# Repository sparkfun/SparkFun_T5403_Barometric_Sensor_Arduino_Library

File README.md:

Sparkfun T5403 Barometric Sensor Breakout Arduino Library
=======================================================

[*SEN-12039*](https://www.sparkfun.com/products/12039)

Library and example code for the Epcos T5403 barometric pressure sensor.

Repository Contents
-------------------

* **/examples** - Example sketches for the library (.ino). Run these from the Arduino IDE. 
* **/src** - Source files for the library (.cpp, .h).
* **keywords.txt** - Keywords from this library that will be highlighted in the Arduino IDE. 
* **library.properties** - General library properties for the Arduino package manager. 

Documentation
--------------
* **[Installing an Arduino Library Guide](https://learn.sparkfun.com/tutorials/installing-an-arduino-library)** - Basic information on how to install an Arduino library.
* **[Product Repository](https://github.com/sparkfun/SparkFun_T5403_Barometric_Breakout)** - Main repository (including hardware files) for the SparkFun T5403 Barometric Sensor Breakout.
* **[Hookup Guide](https://learn.sparkfun.com/tutorials/t5403-barometric-pressure-sensor-hookup)** - Basic hookup guide for the T5403 Barometric Pressure Sensor.

Products that use this Library 
---------------------------------
* [SEN-12039](https://www.sparkfun.com/products/12039) - T5403 Barometric Sensor Breakout

Version History
----------------
* [1.0.1](https://github.com/sparkfun/SparkFun_T5403_Barometric_Sensor_Arduino_Library/tree/V_1.0.1) - Small clean-up, edits.
* [1.0](https://github.com/sparkfun/SparkFun_T5403_Barometric_Sensor_Arduino_Library/tree/V_1.0) - Initial Release

License Information
-------------------

This product is _**open source**_! 

The **code** is beerware; if you see me (or any other SparkFun employee) at the local, and you've found our code helpful, please buy us a round!

Please use, reuse, and modify these files as you see fit. Please maintain attribution to SparkFun Electronics and release anything derivative under the same license.

Distributed as-is; no warranty is given.

- Your friends at SparkFun.

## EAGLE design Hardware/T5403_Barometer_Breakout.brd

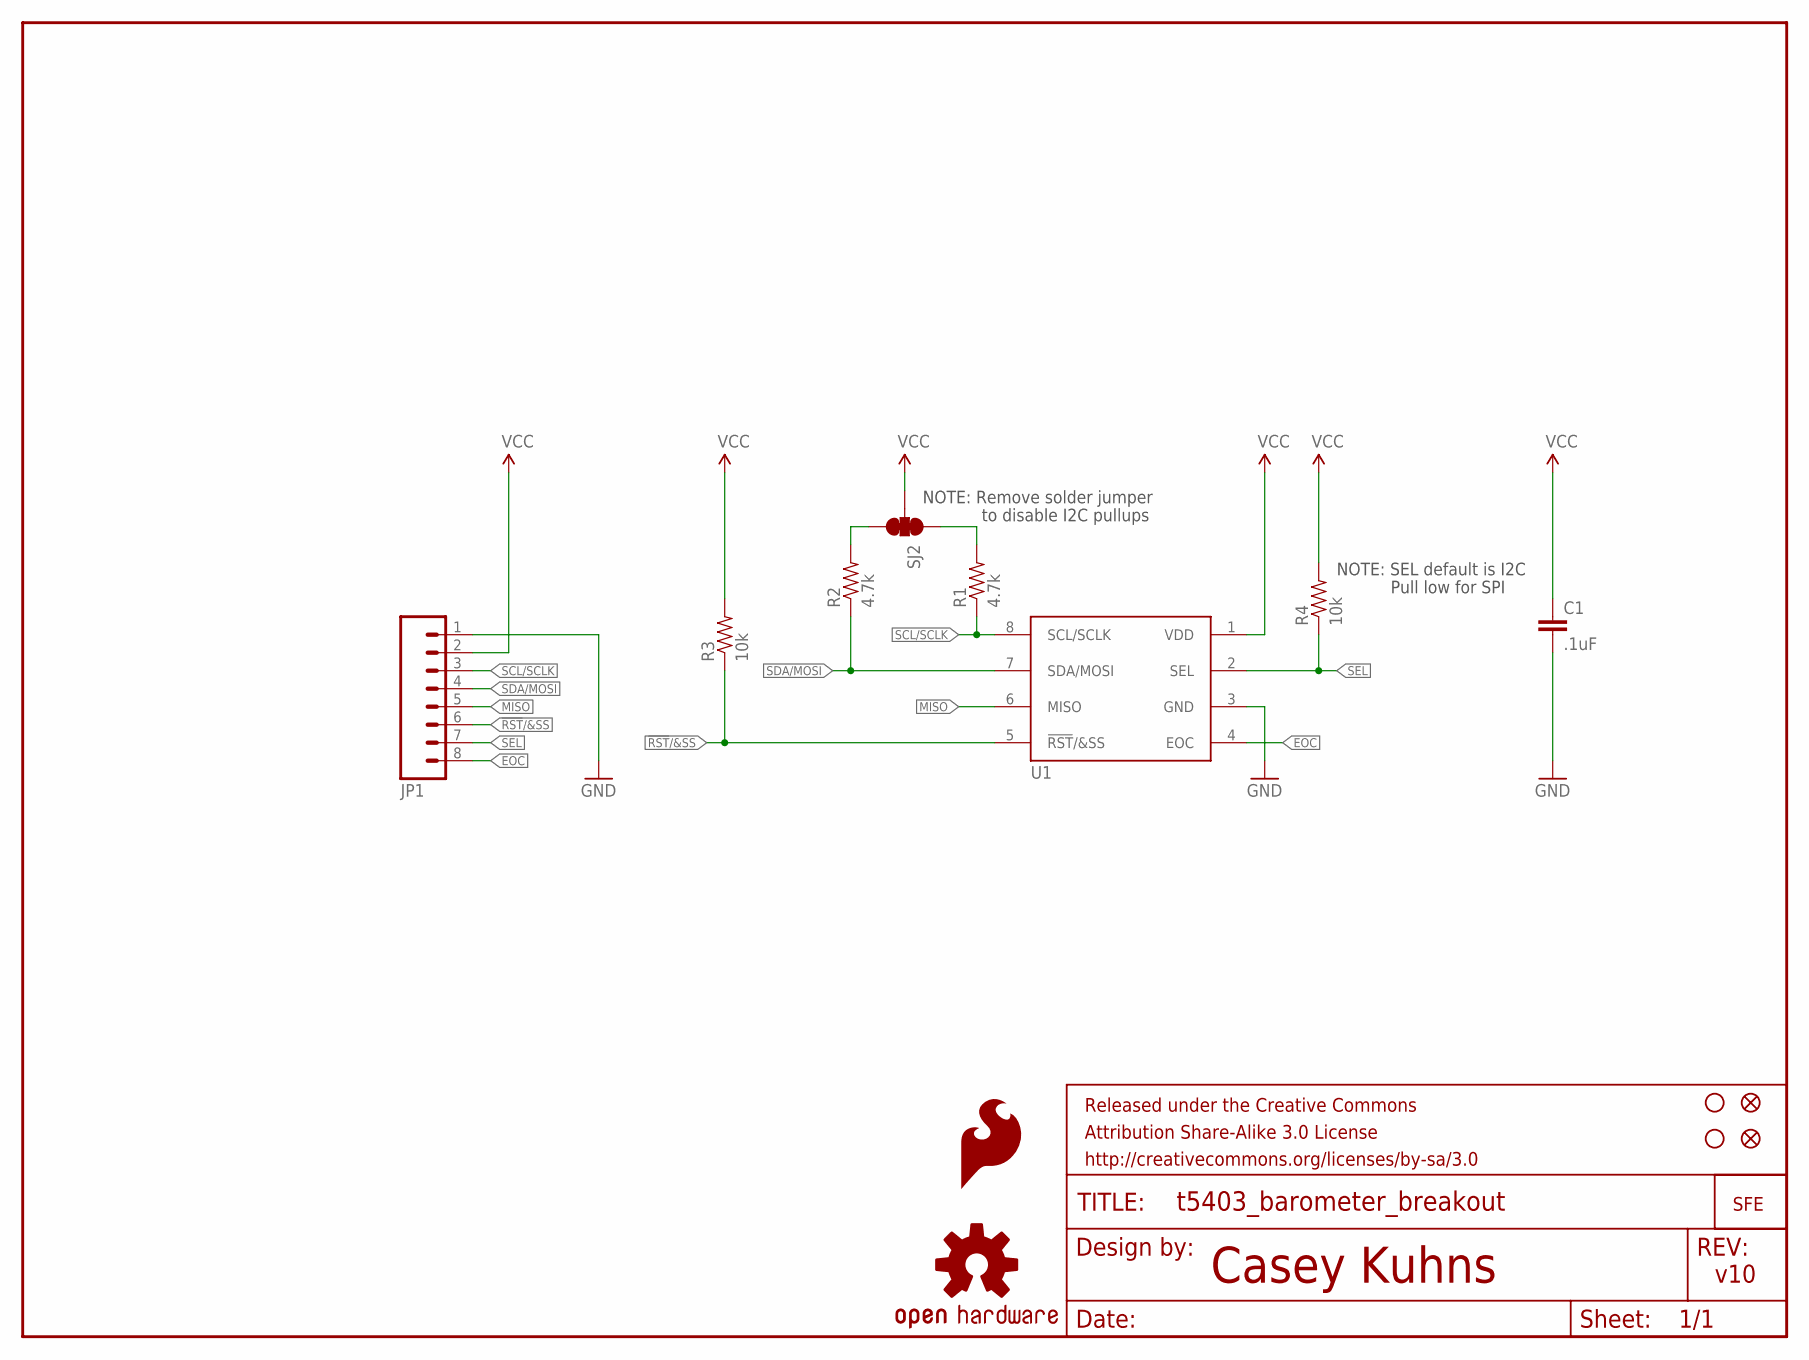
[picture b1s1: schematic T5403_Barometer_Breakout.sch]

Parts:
C1: .1uF; 0603-CAP
FID1, FID2: FIDUCIAL1X2; FIDUCIAL-1X2
FRAME1: FRAME-LETTER; CREATIVE_COMMONS
JP1: M081X08; 1X08
LOGO1: LOGO-SFENEW; SFE-NEW-WEBLOGO
LOGO2: OSHW-LOGOS; OSHW-LOGO-S
LOGO3: SFE_LOGO_FLAME.1_INCH; SFE_LOGO_FLAME_.1
R1, R2: 4.7k; 0603
R3, R4: 10k; 0603-RES
SJ2: SOLDERJUMPER_2WAYPASTE1&2&3; SJ_3_PASTE1&2&3
STANDOFF1, STANDOFF2: STAND-OFF
U1: T5400

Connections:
!RST!/&SS: JP1.6, R3.1, U1.5 (!RST!/&SS)
EOC: JP1.8, U1.4 (EOC)
GND: C1.2, JP1.1, U1.3 (GND)
MISO: JP1.5, U1.6 (MISO)
unnamed: R2.2, SJ2.3
unnamed: R1.2, SJ2.1
SCL/SCLK: JP1.3, R1.1, U1.8 (SCL/SCLK)
SDA/MOSI: JP1.4, R2.1, U1.7 (SDA/MOSI)
SEL: JP1.7, R4.1, U1.2 (SEL)
VCC: C1.1, JP1.2, R3.2, R4.2, SJ2.2, U1.1 (VDD)

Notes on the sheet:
Casey Kuhns
v10
NOTE: Remove solder jumper
to disable I2C pullups
NOTE: SEL default is I2C
Pull low for SPI

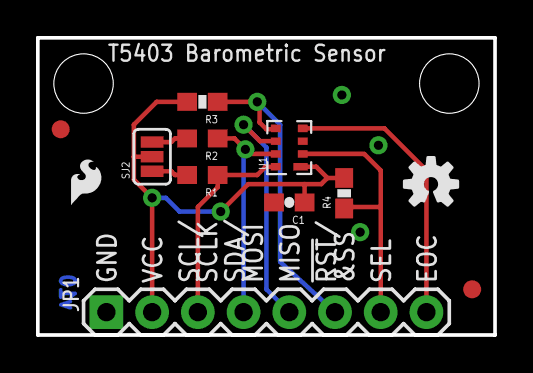
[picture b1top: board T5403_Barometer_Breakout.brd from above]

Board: 2 copper layers, 25.4 x 16.5 mm, 16 parts (1 on the bottom side), 10 nets.

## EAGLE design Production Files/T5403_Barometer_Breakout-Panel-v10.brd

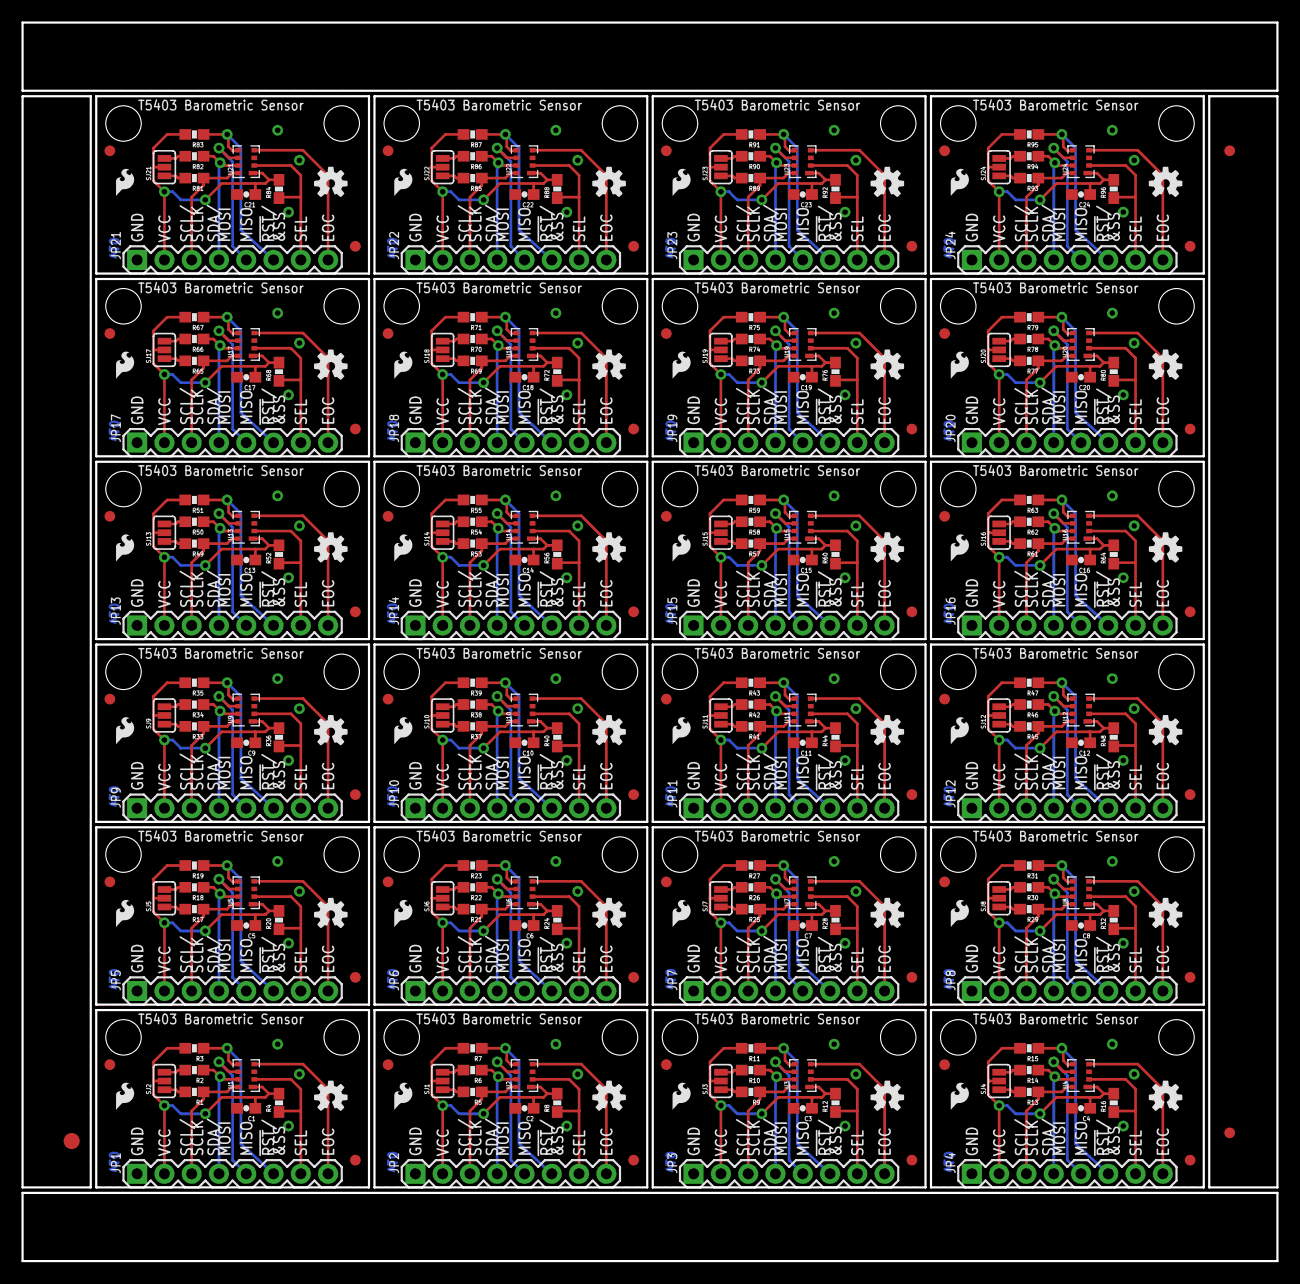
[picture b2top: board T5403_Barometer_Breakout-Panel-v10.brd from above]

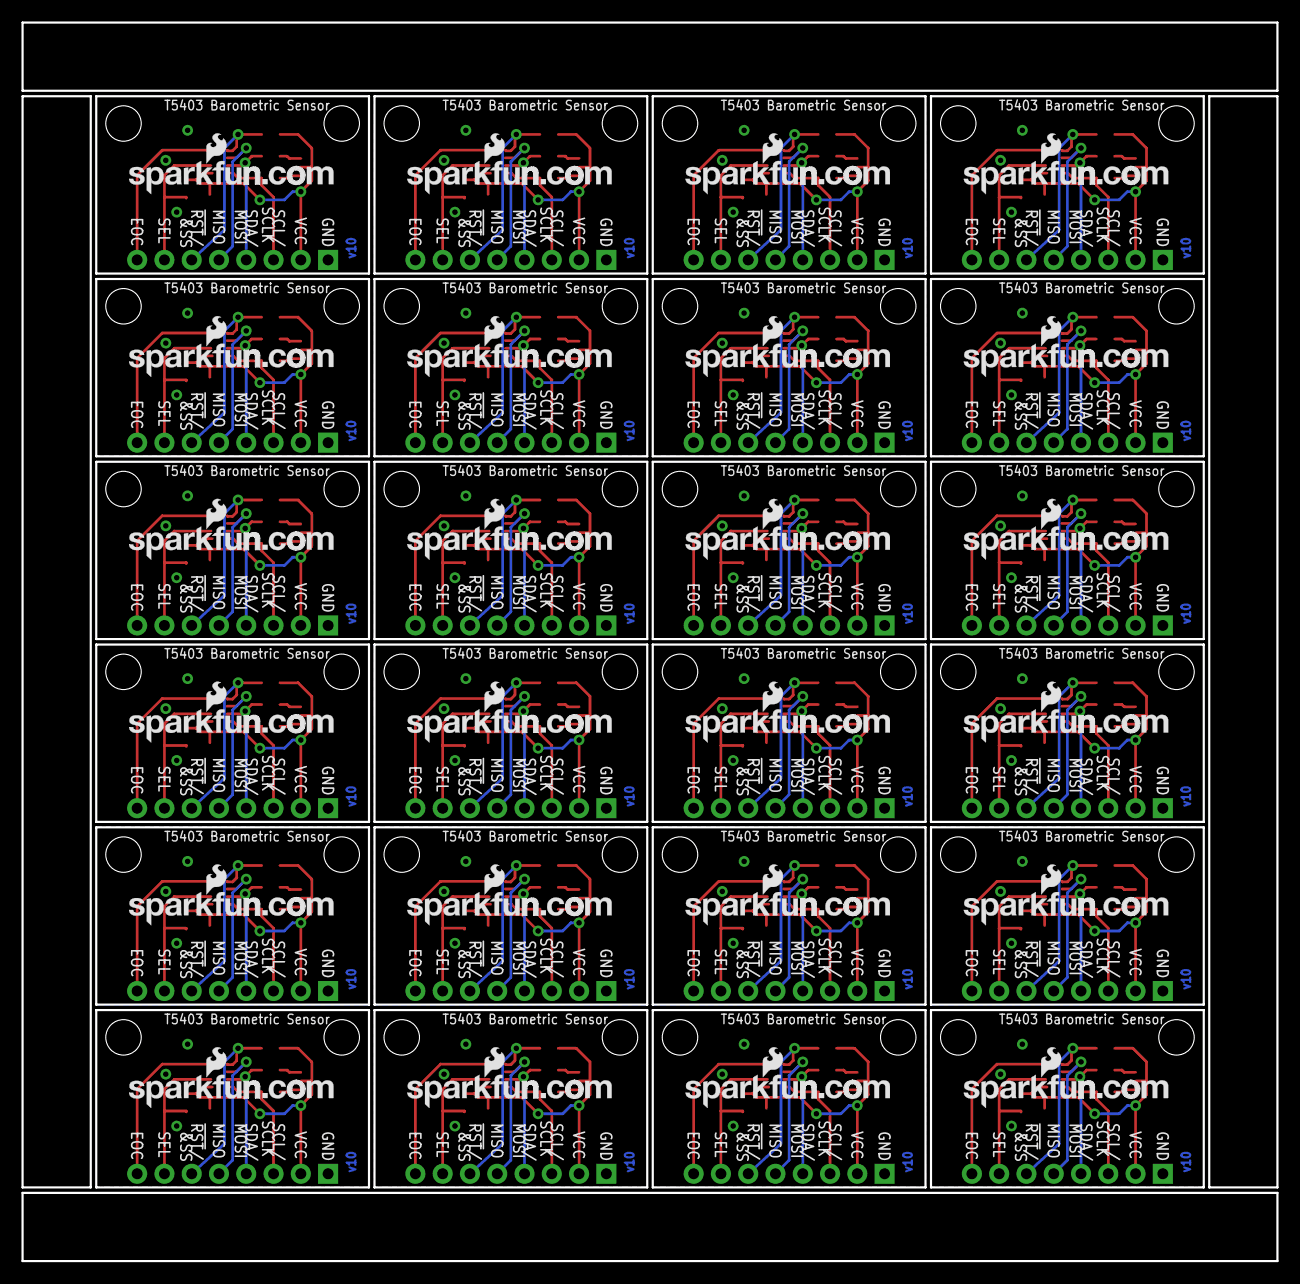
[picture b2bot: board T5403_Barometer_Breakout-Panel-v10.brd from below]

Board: 2 copper layers, 116.8 x 115.3 mm, 363 parts (24 on the bottom side), 240 nets.

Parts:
C1, C2, C3, C4, C5, C6, C7, C8, C9, C10, C11, C12, C13, C14, C15, C16, C17, C18, C19, C20, C21, C22, C23, C24: .1uF; 0603-CAP
E$1: FIDUCIAL-1.5X3
E$4, E$5: FIDUCIAL-1X2
FID1, FID2, FID3, FID4, FID5, FID6, FID7, FID8, FID9, FID10, FID11, FID12, FID13, FID14, FID15, FID16, FID17, FID18, FID19, FID20, FID21, FID22, FID23, FID24, FID25, FID26, FID27, FID28, FID29, FID30, FID31, FID32, FID33, FID34, FID35, FID36, FID37, FID38, FID39, FID40, FID41, FID42, FID43, FID44, FID45, FID46, FID47, FID48: FIDUCIAL1X2; FIDUCIAL-1X2
JP1, JP2, JP3, JP4, JP5, JP6, JP7, JP8, JP9, JP10, JP11, JP12, JP13, JP14, JP15, JP16, JP17, JP18, JP19, JP20, JP21, JP22, JP23, JP24: 1X08
LOGO1, LOGO5, LOGO8, LOGO11, LOGO14, LOGO17, LOGO20, LOGO23, LOGO26, LOGO29, LOGO32, LOGO35, LOGO38, LOGO41, LOGO44, LOGO47, LOGO50, LOGO53, LOGO56, LOGO59, LOGO62, LOGO65, LOGO68, LOGO71: LOGO-SFENEW; SFE-NEW-WEBLOGO
LOGO2, LOGO4, LOGO7, LOGO10, LOGO13, LOGO16, LOGO19, LOGO22, LOGO25, LOGO28, LOGO31, LOGO34, LOGO37, LOGO40, LOGO43, LOGO46, LOGO49, LOGO52, LOGO55, LOGO58, LOGO61, LOGO64, LOGO67, LOGO70: OSHW-LOGOS; OSHW-LOGO-S
LOGO3, LOGO6, LOGO9, LOGO12, LOGO15, LOGO18, LOGO21, LOGO24, LOGO27, LOGO30, LOGO33, LOGO36, LOGO39, LOGO42, LOGO45, LOGO48, LOGO51, LOGO54, LOGO57, LOGO60, LOGO63, LOGO66, LOGO69, LOGO72: SFE_LOGO_FLAME.1_INCH; SFE_LOGO_FLAME_.1
R1, R2, R5, R6, R9, R10, R13, R14, R17, R18, R21, R22, R25, R26, R29, R30, R33, R34, R37, R38, R41, R42, R45, R46, R49, R50, R53, R54, R57, R58, R61, R62, R65, R66, R69, R70, R73, R74, R77, R78, R81, R82, R85, R86, R89, R90, R93, R94: 4.7k; 0603-RES
R3, R4, R7, R8, R11, R12, R15, R16, R19, R20, R23, R24, R27, R28, R31, R32, R35, R36, R39, R40, R43, R44, R47, R48, R51, R52, R55, R56, R59, R60, R63, R64, R67, R68, R71, R72, R75, R76, R79, R80, R83, R84, R87, R88, R91, R92, R95, R96: 10k; 0603-RES
SJ1, SJ2, SJ3, SJ4, SJ5, SJ6, SJ7, SJ8, SJ9, SJ10, SJ11, SJ12, SJ13, SJ14, SJ15, SJ16, SJ17, SJ18, SJ19, SJ20, SJ21, SJ22, SJ23, SJ24: SJ_3_PASTE1&2&3
STANDOFF1, STANDOFF2, STANDOFF3, STANDOFF4, STANDOFF5, STANDOFF6, STANDOFF7, STANDOFF8, STANDOFF9, STANDOFF10, STANDOFF11, STANDOFF12, STANDOFF13, STANDOFF14, STANDOFF15, STANDOFF16, STANDOFF17, STANDOFF18, STANDOFF19, STANDOFF20, STANDOFF21, STANDOFF22, STANDOFF23, STANDOFF24, STANDOFF25, STANDOFF26, STANDOFF27, STANDOFF28, STANDOFF29, STANDOFF30, STANDOFF31, STANDOFF32, STANDOFF33, STANDOFF34, STANDOFF35, STANDOFF36, STANDOFF37, STANDOFF38, STANDOFF39, STANDOFF40, STANDOFF41, STANDOFF42, STANDOFF43, STANDOFF44, STANDOFF45, STANDOFF46, STANDOFF47, STANDOFF48: STAND-OFF
U1, U2, U3, U4, U5, U6, U7, U8, U9, U10, U11, U12, U13, U14, U15, U16, U17, U18, U19, U20, U21, U22, U23, U24: T5400

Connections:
!RST!/&SS: JP1.6, R3.1, U1.5
!RST!/&SS1: JP2.6, R7.1, U2.5
!RST!/&SS2: JP3.6, R11.1, U3.5
!RST!/&SS3: JP4.6, R15.1, U4.5
!RST!/&SS4: JP5.6, R19.1, U5.5
!RST!/&SS5: JP6.6, R23.1, U6.5
!RST!/&SS6: JP7.6, R27.1, U7.5
!RST!/&SS7: JP8.6, R31.1, U8.5
!RST!/&SS8: JP9.6, R35.1, U9.5
!RST!/&SS9: JP10.6, R39.1, U10.5
!RST!/&SS10: JP11.6, R43.1, U11.5
!RST!/&SS11: JP12.6, R47.1, U12.5
!RST!/&SS12: JP13.6, R51.1, U13.5
!RST!/&SS13: JP14.6, R55.1, U14.5
!RST!/&SS14: JP15.6, R59.1, U15.5
!RST!/&SS15: JP16.6, R63.1, U16.5
!RST!/&SS16: JP17.6, R67.1, U17.5
!RST!/&SS17: JP18.6, R71.1, U18.5
!RST!/&SS18: JP19.6, R75.1, U19.5
!RST!/&SS19: JP20.6, R79.1, U20.5
!RST!/&SS20: JP21.6, R83.1, U21.5
!RST!/&SS21: JP22.6, R87.1, U22.5
!RST!/&SS22: JP23.6, R91.1, U23.5
!RST!/&SS23: JP24.6, R95.1, U24.5
EOC: JP1.8, U1.4
EOC1: JP2.8, U2.4
EOC2: JP3.8, U3.4
EOC3: JP4.8, U4.4
EOC4: JP5.8, U5.4
EOC5: JP6.8, U6.4
EOC6: JP7.8, U7.4
EOC7: JP8.8, U8.4
EOC8: JP9.8, U9.4
EOC9: JP10.8, U10.4
EOC10: JP11.8, U11.4
EOC11: JP12.8, U12.4
EOC12: JP13.8, U13.4
EOC13: JP14.8, U14.4
EOC14: JP15.8, U15.4
EOC15: JP16.8, U16.4
EOC16: JP17.8, U17.4
EOC17: JP18.8, U18.4
EOC18: JP19.8, U19.4
EOC19: JP20.8, U20.4
EOC20: JP21.8, U21.4
EOC21: JP22.8, U22.4
EOC22: JP23.8, U23.4
EOC23: JP24.8, U24.4
GND: C1.2, JP1.1, U1.3
GND1: C2.2, JP2.1, U2.3
GND2: C3.2, JP3.1, U3.3
GND3: C4.2, JP4.1, U4.3
GND4: C5.2, JP5.1, U5.3
GND5: C6.2, JP6.1, U6.3
GND6: C7.2, JP7.1, U7.3
GND7: C8.2, JP8.1, U8.3
GND8: C9.2, JP9.1, U9.3
GND9: C10.2, JP10.1, U10.3
GND10: C11.2, JP11.1, U11.3
GND11: C12.2, JP12.1, U12.3
GND12: C13.2, JP13.1, U13.3
GND13: C14.2, JP14.1, U14.3
GND14: C15.2, JP15.1, U15.3
GND15: C16.2, JP16.1, U16.3
GND16: C17.2, JP17.1, U17.3
GND17: C18.2, JP18.1, U18.3
GND18: C19.2, JP19.1, U19.3
GND19: C20.2, JP20.1, U20.3
GND20: C21.2, JP21.1, U21.3
GND21: C22.2, JP22.1, U22.3
GND22: C23.2, JP23.1, U23.3
GND23: C24.2, JP24.1, U24.3
MISO: JP1.5, U1.6
MISO1: JP2.5, U2.6
MISO2: JP3.5, U3.6
MISO3: JP4.5, U4.6
MISO4: JP5.5, U5.6
MISO5: JP6.5, U6.6
MISO6: JP7.5, U7.6
MISO7: JP8.5, U8.6
MISO8: JP9.5, U9.6
MISO9: JP10.5, U10.6
MISO10: JP11.5, U11.6
MISO11: JP12.5, U12.6
MISO12: JP13.5, U13.6
MISO13: JP14.5, U14.6
MISO14: JP15.5, U15.6
MISO15: JP16.5, U16.6
MISO16: JP17.5, U17.6
MISO17: JP18.5, U18.6
MISO18: JP19.5, U19.6
MISO19: JP20.5, U20.6
MISO20: JP21.5, U21.6
MISO21: JP22.5, U22.6
MISO22: JP23.5, U23.6
MISO23: JP24.5, U24.6
unnamed: R2.2, SJ2.3
unnamed: R1.2, SJ2.1
unnamed: R6.2, SJ1.3
unnamed: R5.2, SJ1.1
unnamed: R10.2, SJ3.3
unnamed: R9.2, SJ3.1
unnamed: R14.2, SJ4.3
unnamed: R13.2, SJ4.1
unnamed: R18.2, SJ5.3
unnamed: R17.2, SJ5.1
unnamed: R22.2, SJ6.3
unnamed: R21.2, SJ6.1
unnamed: R26.2, SJ7.3
unnamed: R25.2, SJ7.1
unnamed: R30.2, SJ8.3
unnamed: R29.2, SJ8.1
unnamed: R34.2, SJ9.3
unnamed: R33.2, SJ9.1
unnamed: R38.2, SJ10.3
unnamed: R37.2, SJ10.1
unnamed: R42.2, SJ11.3
unnamed: R41.2, SJ11.1
unnamed: R46.2, SJ12.3
unnamed: R45.2, SJ12.1
unnamed: R50.2, SJ13.3
unnamed: R49.2, SJ13.1
unnamed: R54.2, SJ14.3
unnamed: R53.2, SJ14.1
unnamed: R58.2, SJ15.3
unnamed: R57.2, SJ15.1
unnamed: R62.2, SJ16.3
unnamed: R61.2, SJ16.1
unnamed: R66.2, SJ17.3
unnamed: R65.2, SJ17.1
unnamed: R70.2, SJ18.3
unnamed: R69.2, SJ18.1
unnamed: R74.2, SJ19.3
unnamed: R73.2, SJ19.1
unnamed: R78.2, SJ20.3
unnamed: R77.2, SJ20.1
unnamed: R82.2, SJ21.3
unnamed: R81.2, SJ21.1
unnamed: R86.2, SJ22.3
unnamed: R85.2, SJ22.1
unnamed: R90.2, SJ23.3
unnamed: R89.2, SJ23.1
unnamed: R94.2, SJ24.3
unnamed: R93.2, SJ24.1
SCL/SCLK: JP1.3, R1.1, U1.8
SCL/SCLK1: JP2.3, R5.1, U2.8
SCL/SCLK2: JP3.3, R9.1, U3.8
SCL/SCLK3: JP4.3, R13.1, U4.8
SCL/SCLK4: JP5.3, R17.1, U5.8
SCL/SCLK5: JP6.3, R21.1, U6.8
SCL/SCLK6: JP7.3, R25.1, U7.8
SCL/SCLK7: JP8.3, R29.1, U8.8
SCL/SCLK8: JP9.3, R33.1, U9.8
SCL/SCLK9: JP10.3, R37.1, U10.8
SCL/SCLK10: JP11.3, R41.1, U11.8
SCL/SCLK11: JP12.3, R45.1, U12.8
SCL/SCLK12: JP13.3, R49.1, U13.8
SCL/SCLK13: JP14.3, R53.1, U14.8
SCL/SCLK14: JP15.3, R57.1, U15.8
SCL/SCLK15: JP16.3, R61.1, U16.8
SCL/SCLK16: JP17.3, R65.1, U17.8
SCL/SCLK17: JP18.3, R69.1, U18.8
SCL/SCLK18: JP19.3, R73.1, U19.8
SCL/SCLK19: JP20.3, R77.1, U20.8
SCL/SCLK20: JP21.3, R81.1, U21.8
SCL/SCLK21: JP22.3, R85.1, U22.8
SCL/SCLK22: JP23.3, R89.1, U23.8
SCL/SCLK23: JP24.3, R93.1, U24.8
SDA/MOSI: JP1.4, R2.1, U1.7
SDA/MOSI1: JP2.4, R6.1, U2.7
SDA/MOSI2: JP3.4, R10.1, U3.7
SDA/MOSI3: JP4.4, R14.1, U4.7
SDA/MOSI4: JP5.4, R18.1, U5.7
SDA/MOSI5: JP6.4, R22.1, U6.7
SDA/MOSI6: JP7.4, R26.1, U7.7
SDA/MOSI7: JP8.4, R30.1, U8.7
SDA/MOSI8: JP9.4, R34.1, U9.7
SDA/MOSI9: JP10.4, R38.1, U10.7
SDA/MOSI10: JP11.4, R42.1, U11.7
SDA/MOSI11: JP12.4, R46.1, U12.7
SDA/MOSI12: JP13.4, R50.1, U13.7
SDA/MOSI13: JP14.4, R54.1, U14.7
SDA/MOSI14: JP15.4, R58.1, U15.7
SDA/MOSI15: JP16.4, R62.1, U16.7
SDA/MOSI16: JP17.4, R66.1, U17.7
SDA/MOSI17: JP18.4, R70.1, U18.7
SDA/MOSI18: JP19.4, R74.1, U19.7
SDA/MOSI19: JP20.4, R78.1, U20.7
SDA/MOSI20: JP21.4, R82.1, U21.7
SDA/MOSI21: JP22.4, R86.1, U22.7
SDA/MOSI22: JP23.4, R90.1, U23.7
SDA/MOSI23: JP24.4, R94.1, U24.7
SEL: JP1.7, R4.1, U1.2
SEL1: JP2.7, R8.1, U2.2
SEL2: JP3.7, R12.1, U3.2
SEL3: JP4.7, R16.1, U4.2
SEL4: JP5.7, R20.1, U5.2
SEL5: JP6.7, R24.1, U6.2
SEL6: JP7.7, R28.1, U7.2
SEL7: JP8.7, R32.1, U8.2
SEL8: JP9.7, R36.1, U9.2
SEL9: JP10.7, R40.1, U10.2
SEL10: JP11.7, R44.1, U11.2
SEL11: JP12.7, R48.1, U12.2
SEL12: JP13.7, R52.1, U13.2
SEL13: JP14.7, R56.1, U14.2
SEL14: JP15.7, R60.1, U15.2
SEL15: JP16.7, R64.1, U16.2
SEL16: JP17.7, R68.1, U17.2
SEL17: JP18.7, R72.1, U18.2
SEL18: JP19.7, R76.1, U19.2
SEL19: JP20.7, R80.1, U20.2
SEL20: JP21.7, R84.1, U21.2
SEL21: JP22.7, R88.1, U22.2
SEL22: JP23.7, R92.1, U23.2
SEL23: JP24.7, R96.1, U24.2
VCC: C1.1, JP1.2, R3.2, R4.2, SJ2.2, U1.1
VCC1: C2.1, JP2.2, R7.2, R8.2, SJ1.2, U2.1
VCC2: C3.1, JP3.2, R11.2, R12.2, SJ3.2, U3.1
VCC3: C4.1, JP4.2, R15.2, R16.2, SJ4.2, U4.1
VCC4: C5.1, JP5.2, R19.2, R20.2, SJ5.2, U5.1
VCC5: C6.1, JP6.2, R23.2, R24.2, SJ6.2, U6.1
VCC6: C7.1, JP7.2, R27.2, R28.2, SJ7.2, U7.1
VCC7: C8.1, JP8.2, R31.2, R32.2, SJ8.2, U8.1
VCC8: C9.1, JP9.2, R35.2, R36.2, SJ9.2, U9.1
VCC9: C10.1, JP10.2, R39.2, R40.2, SJ10.2, U10.1
VCC10: C11.1, JP11.2, R43.2, R44.2, SJ11.2, U11.1
VCC11: C12.1, JP12.2, R47.2, R48.2, SJ12.2, U12.1
VCC12: C13.1, JP13.2, R51.2, R52.2, SJ13.2, U13.1
VCC13: C14.1, JP14.2, R55.2, R56.2, SJ14.2, U14.1
VCC14: C15.1, JP15.2, R59.2, R60.2, SJ15.2, U15.1
VCC15: C16.1, JP16.2, R63.2, R64.2, SJ16.2, U16.1
VCC16: C17.1, JP17.2, R67.2, R68.2, SJ17.2, U17.1
VCC17: C18.1, JP18.2, R71.2, R72.2, SJ18.2, U18.1
VCC18: C19.1, JP19.2, R75.2, R76.2, SJ19.2, U19.1
VCC19: C20.1, JP20.2, R79.2, R80.2, SJ20.2, U20.1
VCC20: C21.1, JP21.2, R83.2, R84.2, SJ21.2, U21.1
VCC21: C22.1, JP22.2, R87.2, R88.2, SJ22.2, U22.1
VCC22: C23.1, JP23.2, R91.2, R92.2, SJ23.2, U23.1
VCC23: C24.1, JP24.2, R95.2, R96.2, SJ24.2, U24.1

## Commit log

2013-08-16 Added woot!
2013-08-20 Added board files for review
2013-08-20 Fixed file error
2013-08-21 corrected file names to reflect PROTO status made minor modifications to apperance
2013-08-27 READY for proto
    Corrected boards per meeting agenda. Also changed names
2013-08-27 removed fiducials
2013-10-01 Corrected silk in BRD to reflect proper pin outs. Added library for review and example file for testing. Still need work on SPI support
    modified: Hardware/T5400_Barometer_Breakout.brd
    modified: Hardware/T5400_Barometer_Breakout.sch
    new file: Libraries/README.md.txt
    new file: Libraries/T5400/keywords.txt
    new file: Libraries/T5400/t5400.cpp
    new file: Libraries/T5400/t5400.h
2013-10-28 updated with mode pullup and larger board
2013-11-05 changed version and modified pads for production
2013-11-05 Created Panel
2013-11-12 Changed Name to reflect new chip version
2013-11-13 Recreated Panel
2013-11-13 Name changes on files
    reflecting different IC (5403)
2013-12-12 Cleaned up file names to reflect t5400 - t5403 switch
2013-12-12 Forgot to rename the folder to t5403 all sub files are the same
2014-02-13 updated Library, Need to finish commenting and demo sketch
2014-02-19 continued editing library, added Fritzing files
2014-02-20 cleaned up comments in .h and .cpp TODO: finish demo code.
2014-02-21 updated demo code
2014-02-21 removed status from Wire calls
2014-03-05 Renaming files
2014-03-05 added documentation
2014-03-06 added fritzing files
2014-03-06 fixed Library names and delay values
2014-03-25 cleaned up SCH and replaced components with correct Sparkle ID's
2015-04-24 moved Arduino Library from board repo to new repo for arduino library compatibility
2015-05-14 Fixing minor typos and naming conventions
2015-05-14 Fixing compile error
2015-05-14 Update SparkFunT5403.cpp
    Changing the value of commanded_precision causes the switch statement below to never match any of the cases.

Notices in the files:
parts and their libraries:
SparkFun-Connectors: Licensing: CC v3.0 Share-Alike You are welcome to use this library for commercial purposes.
SparkFun-Aesthetics: Released under the Creative Commons Attribution Share-Alike 3.0 License
SparkFun-Aesthetics: http://creativecommons.org/licenses/by-sa/3.0
